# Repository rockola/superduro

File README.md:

# superduro
Superduro PCB, yet another Super Hard On clone

* v0.1: initial import, complete, unverified
* v0.2: Rick Holt's "Superheated SHO", verified

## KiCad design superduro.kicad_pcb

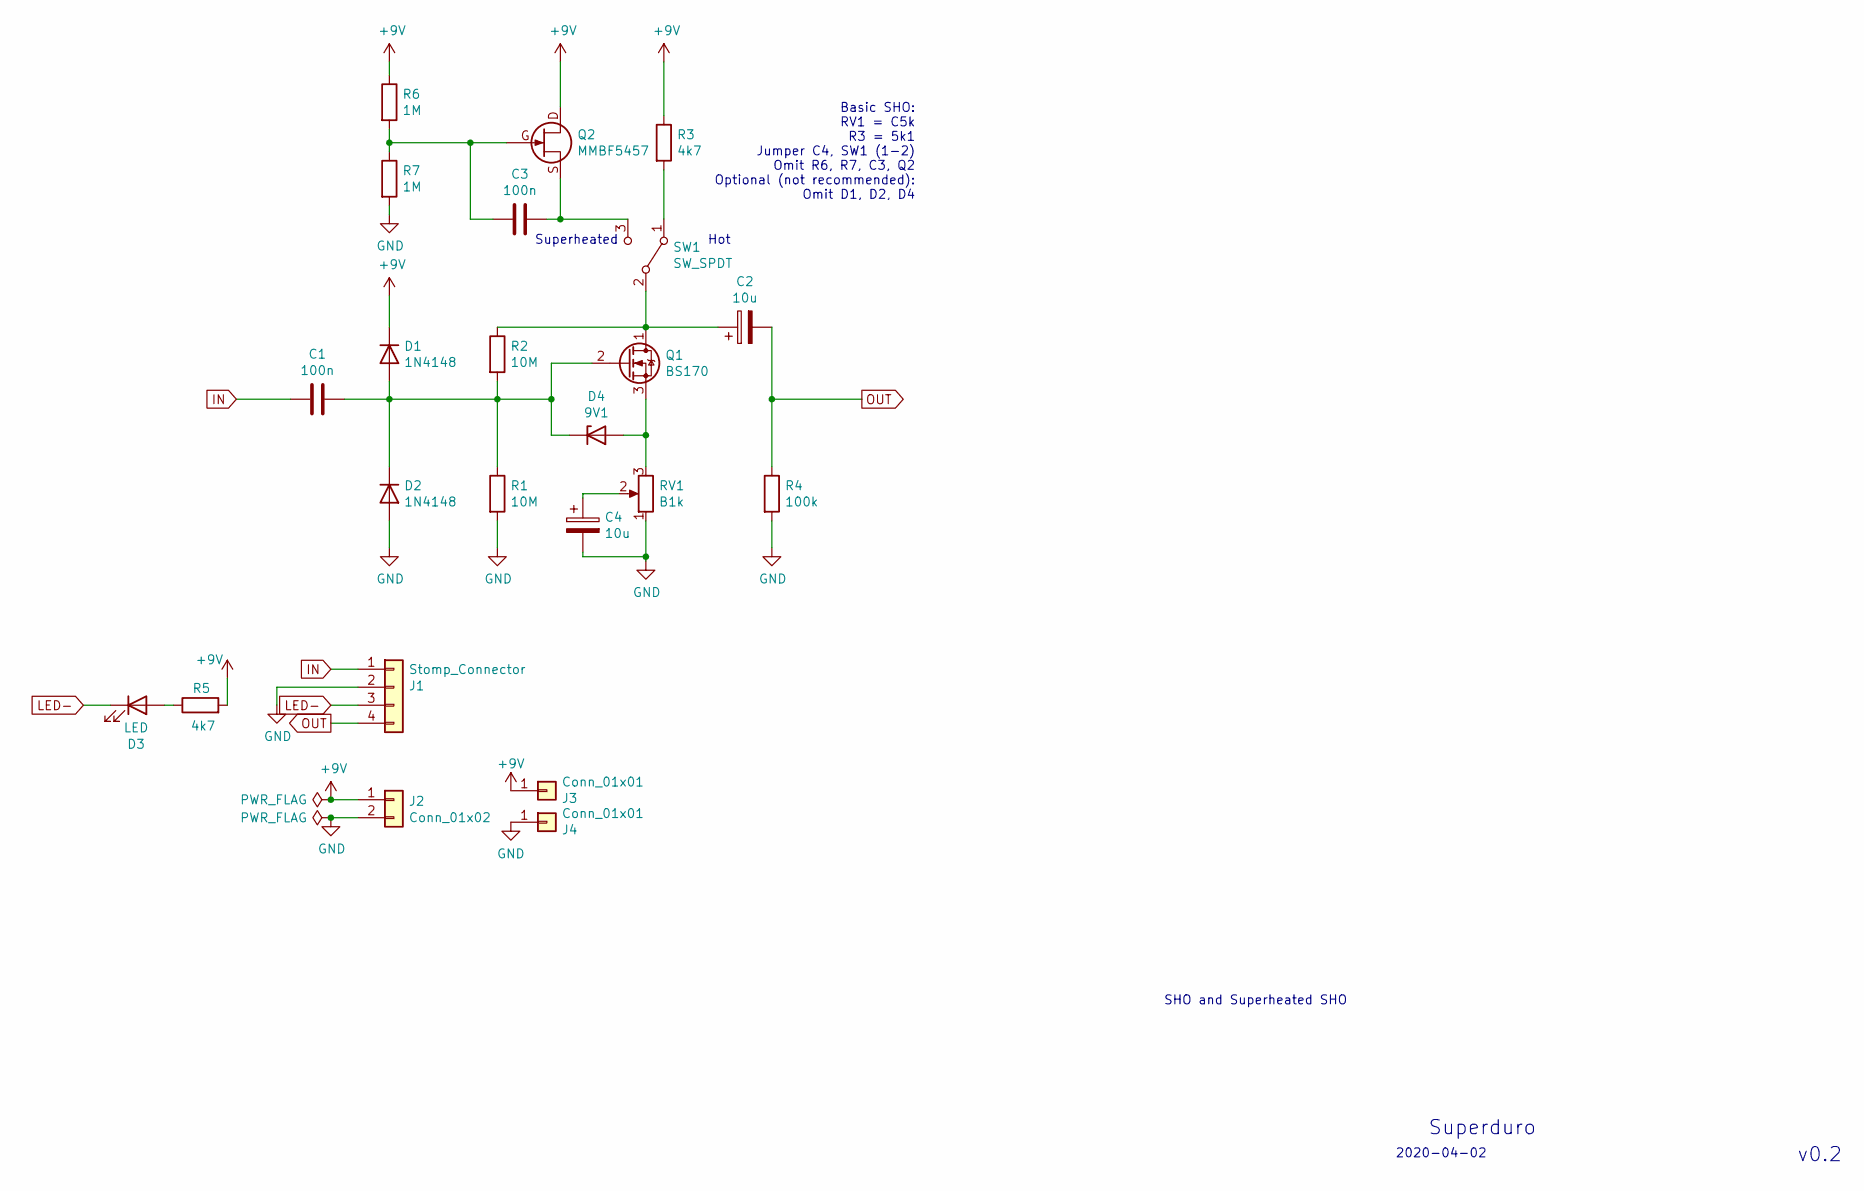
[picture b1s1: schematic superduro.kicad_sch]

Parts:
C1, C3: 100n; C_Box_7.2_2.5
C2, C4: 10u; 0502
D1, D2: 1N4148; DO35-3
D3: LED; LED_D3.0mm
D4: 9V1; DO41-3
J1: Stomp_Connector; Stomp_4pin_ALT2
J2: Conn_01x02; Power_Header_2pin_VERTICAL
J3: Conn_01x01; V+_TOP_TEXT
J4: Conn_01x01; PAD1
Q1: BS170; TO92_DGS
Q2: MMBF5457; SOT-23_NJFET_DSG
R1, R2: 10M; 0.3%22.B
R3, R5: 4k7; 0.3%22.B
R4: 100k; 0.3%22.B
R6, R7: 1M; 0.3%22.B
RV1: B1k; 16mm_BoardMount
SW1: SW_SPDT; SPDT.WIRE

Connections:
+9V: D1.1 (K), J2.1, J3.1, Q2.D, R3.1, R5.2, R6.1
GND: C4.2, D2.2 (A), J1.2 (GND), J2.2, J4.1, R1.2, R4.2, R7.2, RV1.1
IN: C1.1, J1.1 (IN)
LED-: D3.1 (K), J1.3 (SW)
unnamed: C1.2, D1.2 (A), D2.1 (K), D4.1 (K), Q1.2 (G), R1.1, R2.2
unnamed: C2.1, Q1.1 (D), R2.1, SW1.2 (B)
unnamed: C3.1, Q2.G, R6.2, R7.1
unnamed: C3.2, Q2.S, SW1.3 (C)
unnamed: C4.1, RV1.2
unnamed: D3.2 (A), R5.1
unnamed: D4.2 (A), Q1.3 (S), RV1.3
unnamed: R3.2, SW1.1 (A)
OUT: C2.2, J1.4 (OUT), R4.1

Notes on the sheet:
Superduro
Superheated
v0.2
SHO and Superheated SHO
Basic SHO: RV1 = C5k R3 = 5k1 Jumper C4, SW1 (1-2) Omit R6, R7, C3, Q2 Optional (not recommended): Omit D1, D2, D4
Hot
2020-04-02

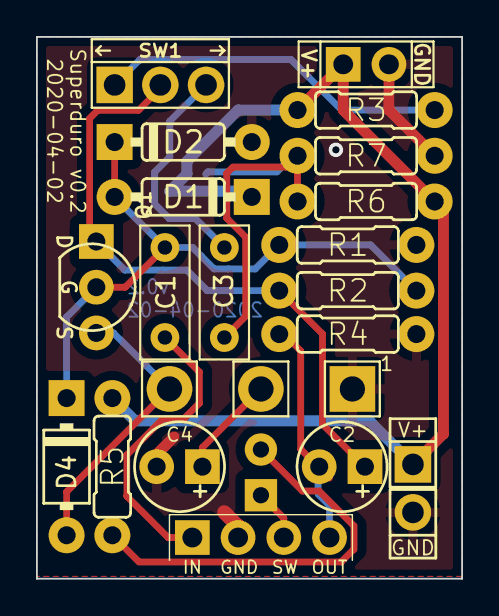
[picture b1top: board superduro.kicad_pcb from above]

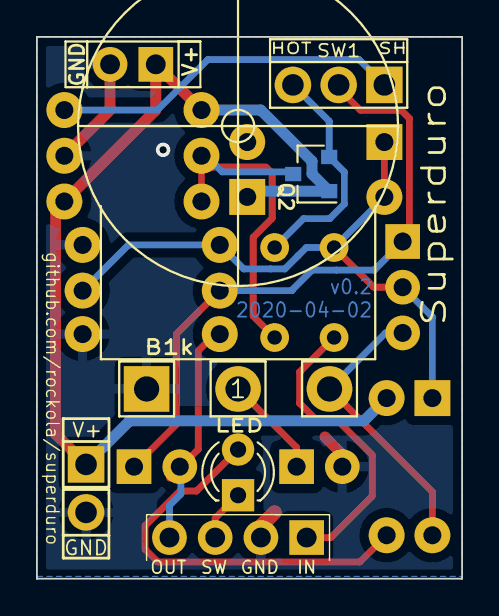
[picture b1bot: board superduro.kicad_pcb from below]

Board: 2 copper layers, 23.6 x 30.1 mm, 23 parts (2 on the bottom side), 13 nets.

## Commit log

2020-02-24 KiCAD & Emacs ignores
2020-02-24 initial
2020-02-24 added in/out/pwr jacks
2020-03-21 v0.1: initial version
2020-03-21 v0.1 pcb images from oshpark
2020-03-21 v0.1: initial
2020-04-02 just Gerber output settings
2020-04-02 v0.2: Superheated SHO
2020-04-02 0.2 images
2022-01-11 ignore backups directory
2022-01-11 updated to KiCad 6.0
